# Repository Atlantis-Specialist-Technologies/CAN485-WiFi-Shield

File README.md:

SparkFun AST-CAN485 WiFi Shield
========================================

[*SparkFun AST-CAN485 WiFi Shield (14597)*](https://www.sparkfun.com/products/14597)

The [AST-CAN485 Dev Board](https://www.sparkfun.com/products/14483) brings CAN (Control Area Network) and RS485 to a small, Pro Mini form factor with the ability to interface to 24V input and outputs. When looking to save space, losing the communication cable is one of the best options as well. The SparkFun AST-CAN485 WiFi Shield does just that. With Screw terminal connectors for RS-485 and a U.FL connector, this board supplies solid solutions for working wirelessly in automation, an environment famous for being noisy and unforgiving to electronics. 

The board uses Espressif's ESP8266, a widely used chip in IoT, for wireless communication. The AST-CAN485 WiFi Shield possesses a PCB trace antenna as well as an on-board U.FL connector which allows for external WiFi antennas in situations where more signal strength or distance is needed. An FTDI header is provided as well for working with the ESP8266.

Repository Contents
-------------------

* **/Documentation** - Data sheets, additional product information
* **/Examples/BasicSerial** - Enclosure files 
* **/Hardware** - Eagle design files (.brd, .sch)

Documentation
--------------
* **[Hookup Guide](https://learn.sparkfun.com/tutorials/ast-can485-wifi-shield-hookup-guide)** - Basic hookup guide for the SparkFun AST-CAN485 WiFi Shield.
* **[SparkFun Fritzing repo](https://github.com/sparkfun/Fritzing_Parts)** - Fritzing diagrams for SparkFun products.

License Information
-------------------

This product is _**open source**_! 

Please review the LICENSE.md file for license information. 

If you have any questions or concerns on licensing, please contact techsupport@sparkfun.com.

Distributed as-is; no warranty is given.

- Your friends at SparkFun, in collaboration with Atlantis Specialist Technologies

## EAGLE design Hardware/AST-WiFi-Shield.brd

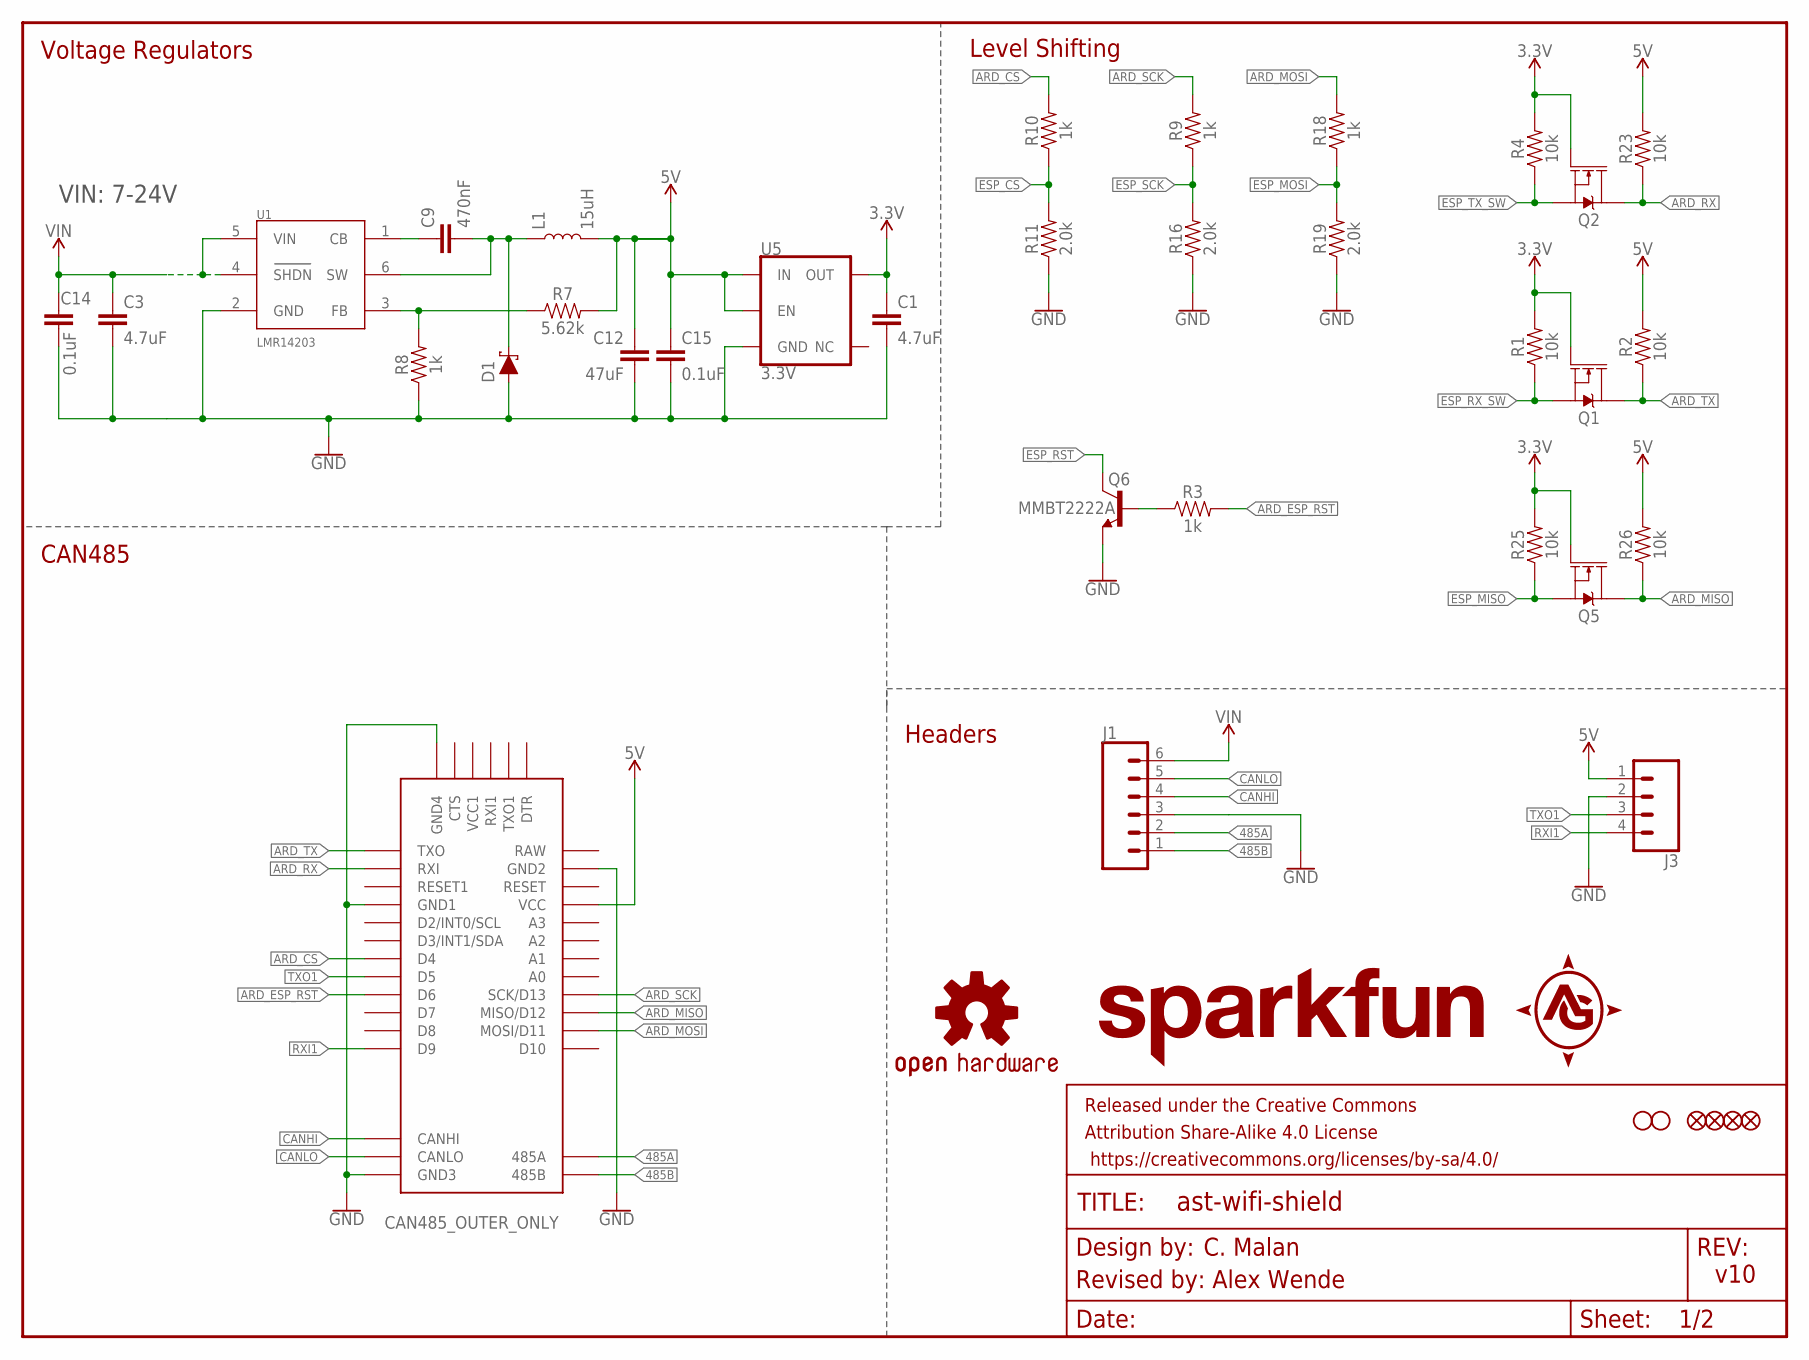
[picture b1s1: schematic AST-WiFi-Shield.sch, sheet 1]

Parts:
C1, C3: 4.7uF; 0603
C9: 470nF; 0603
C12: 47uF; 0805
C14, C15: 0.1uF; 0603
D1: DIODE-SCHOTTKY-MSS1P6-M3/89A; DIODE-MICRO-SMP
FD1, FD2, FD3, FD4: FIDUCIALUFIDUCIAL; FIDUCIAL-MICRO
FRAME2: FRAME-LETTER; CREATIVE_COMMONS
H1, H2: STAND-OFF
J1: CONN_063.5MM-6; SCREWTERMINAL-3.5MM-6
J3: CONN_04LOCK; 1X04_LOCK
L1: 15uH; INDUCTOR_LQH32
LOGO1: OSHW-LOGOS; OSHW-LOGO-S
LOGO2: SFE_LOGO_NAME.2_INCH; SFE_LOGO_NAME_.2
Q1, Q2, Q5: 220mA/50V/3.5Ω; SOT23-3
Q6: MMBT2222A; SOT23-3@1
R1, R2, R4, R23, R25, R26: 10k; 0603
R3, R8, R9, R10, R18: 1k; 0603
R7: 5.62k; 0603
R11, R16, R19: 2.0k; 0603
U1: LMR14203; SOT23-6
U5: 3.3V; SOT23-5
U$2: CAN485_OUTER_ONLY

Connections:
3.3V: C1.1, Q1.1 (G), Q2.1 (G), Q5.1 (G), R1.2, R4.2, R25.2, U5.5 (OUT); also elsewhere on the board
5V: C12.1, C15.1, J3.1, L1.P$2 (2), R2.2, R7.2, R23.2, R26.2, U5.1 (IN), U5.3 (EN), U$2.VCC
485A: J1.2, U$2.485A
485B: J1.1, U$2.485B
ARD_CS: R10.2, U$2.4 (D4)
ARD_ESP_RST: R3.2, U$2.6 (D6)
ARD_MISO: Q5.3 (D), R26.1, U$2.12 (MISO/D12)
ARD_MOSI: R18.2, U$2.11 (MOSI/D11)
ARD_RX: Q2.3 (D), R23.1, U$2.RXI
ARD_SCK: R9.2, U$2.13 (SCK/D13)
ARD_TX: Q1.3 (D), R2.1, U$2.TXO
CANHI: J1.4, U$2.CANHI
CANLO: J1.5, U$2.CANLO
ESP_CS: R10.1, R11.2; also elsewhere on the board
ESP_MISO: Q5.2 (S), R25.1; also elsewhere on the board
ESP_MOSI: R18.1, R19.2; also elsewhere on the board
ESP_RST: Q6.3 (C); also elsewhere on the board
ESP_RX_SW: Q1.2 (S), R1.1; also elsewhere on the board
ESP_SCK: R9.1, R16.2; also elsewhere on the board
ESP_TX_SW: Q2.2 (S), R4.1; also elsewhere on the board
GND: C1.2, C3.2, C12.2, C14.2, C15.2, D1.A, J1.3, J3.2, Q6.2 (E), R8.1, R11.1, R16.1, R19.1, U1.2 (GND), U5.2 (GND), U$2.GND1, U$2.GND2, U$2.GND3, U$2.GND4; also elsewhere on the board
unnamed: C9.1, U1.1 (CB)
unnamed: R7.1, R8.2, U1.3 (FB)
unnamed: Q6.1 (B), R3.1
RXI1: J3.4, U$2.9 (D9)
TXO1: J3.3, U$2.5 (D5)
VIN: C3.1, C14.1, J1.6, U1.4 (SHDN), U1.5 (VIN)
VSW: C9.2, D1.C, L1.P$1 (1), U1.6 (SW)

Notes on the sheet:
Headers
Voltage Regulators
Level Shifting
C. Malan
Revised by: Alex Wende
CAN485
v10
VIN: 7-24V

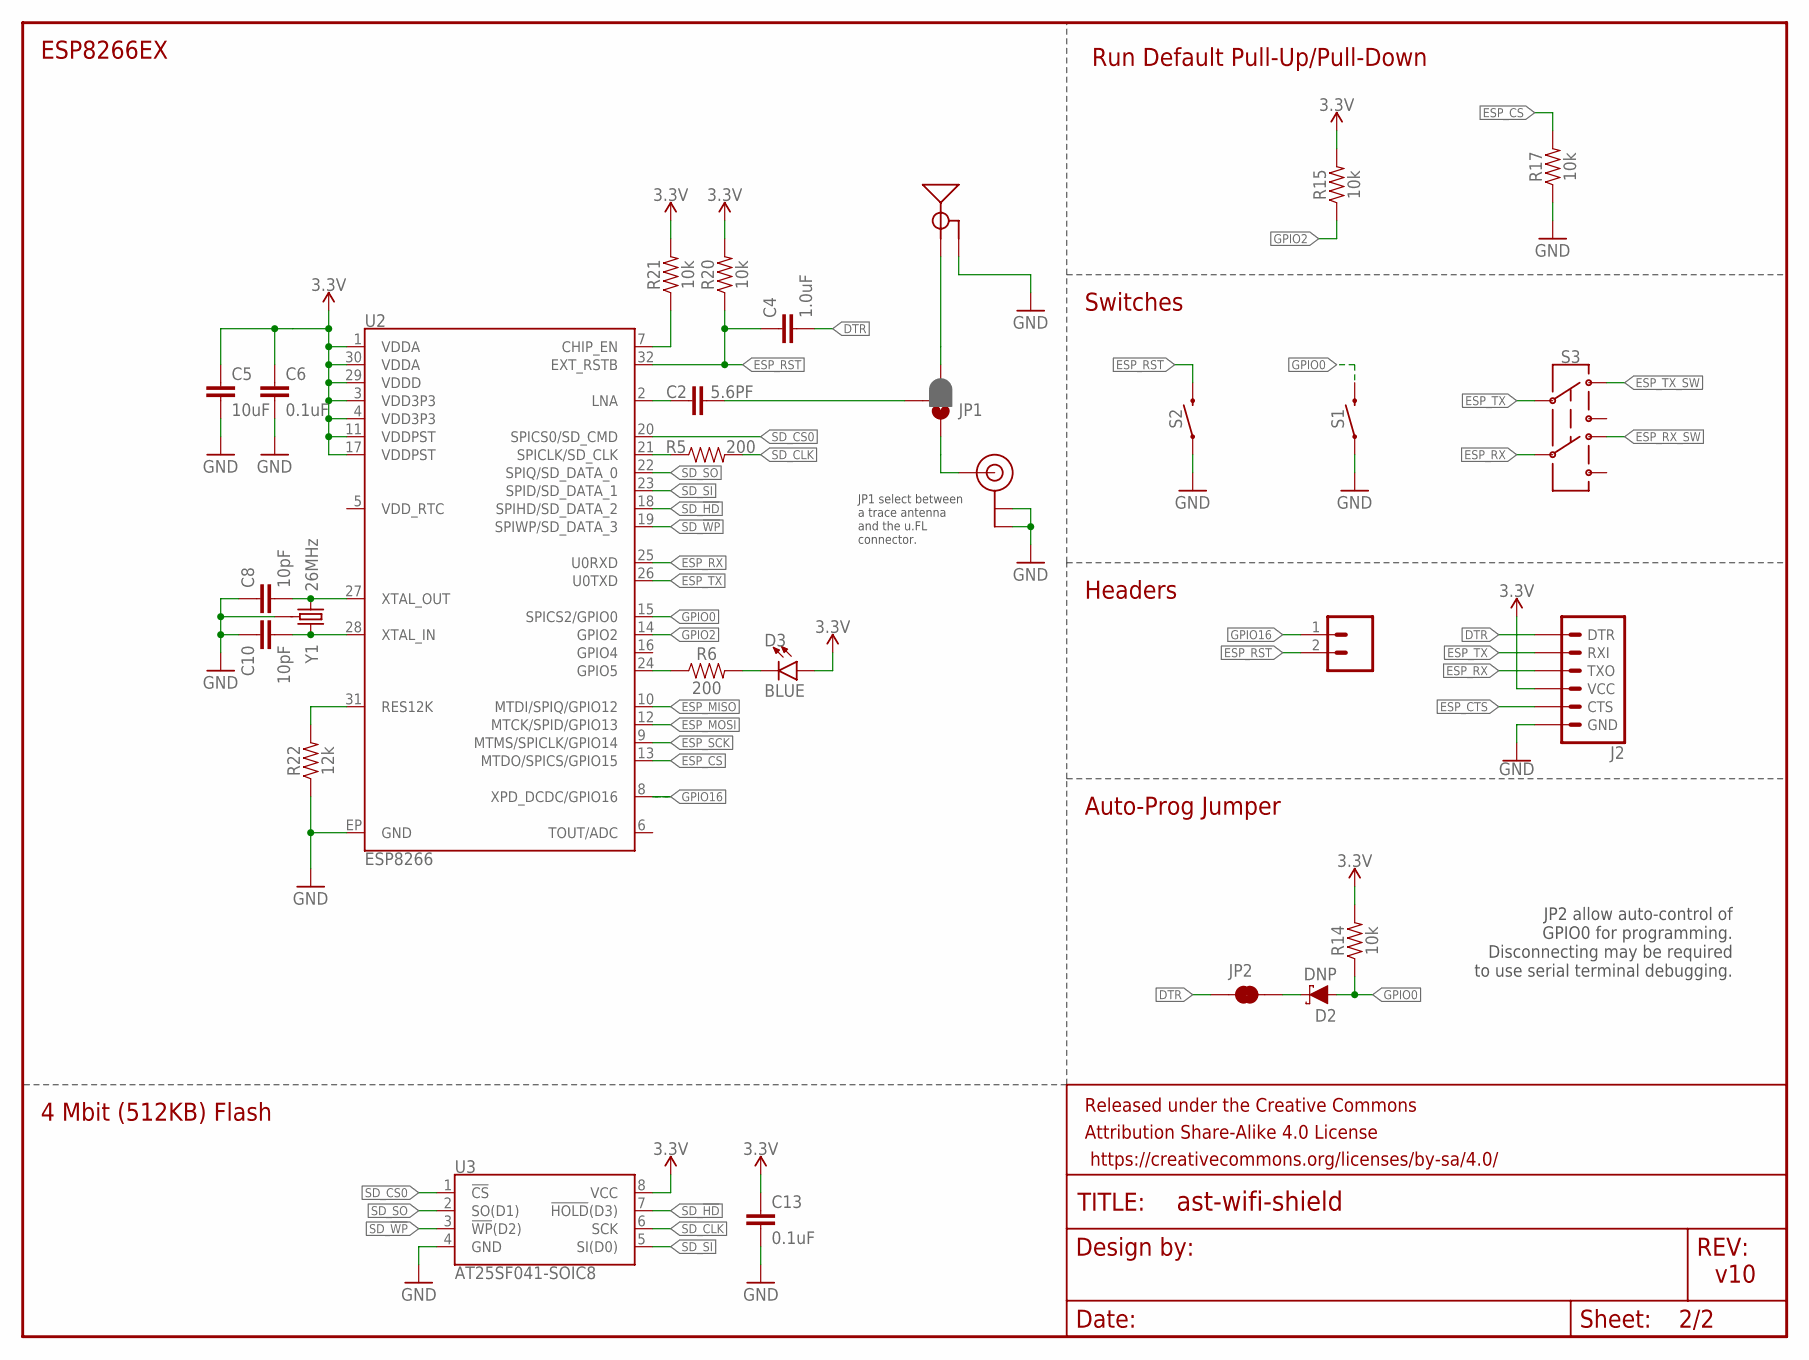
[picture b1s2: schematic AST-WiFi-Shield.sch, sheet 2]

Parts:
C2: 5.6PF; 0603
C4: 1.0uF; 0603
C5: 10uF; 0603
C6, C13: 0.1uF; 0603
C8, C10: 10pF; 0603
D2: DNP; SOD-323
D3: BLUE; LED-0603
E1: ANTENNATRACE; TRACE_ANTENNA_2.4GHZ_25.7MM
E2: U.FL
FRAME3: FRAME-LETTERNO_PACKAGE; DUMMY
J2: 6_PIN_SERIAL_TARGETLOCK; 1X06_LOCK
JP1: JUMPER-SMT_3_1-NC_PASTE_NO-SILK; SMT-JUMPER_3_1-NC_PASTE_NO-SILK
JP2: JUMPER-SMT_2_NC_TRACE_NO-SILK; SMT-JUMPER_2_NC_TRACE_NO-SILK
R5, R6: 200; 0603
R14, R15, R17, R20, R21: 10k; 0603
R22: 12k; 0603
S1, S2: MOMENTARY-SWITCH-SPST-SMD-4.6X2.8MM; TACTILE_SWITCH_SMD_4.6X2.8MM
S3: SWITCH-DPDT-SMD-JS202011JCQN; SWITCH_DPDT_SMD_JS202011JCQN
SJ2: SLEEP-PTH; 1X02_NO_SILK
U2: ESP8266; QFN32
U3: AT25SF041-SOIC8; SO08
Y1: 26MHz; CRYSTAL-SMD-3.2X2.5

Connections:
3.3V: C5.1, C6.1, C13.1, D3.A, J2.4 (VCC), R14.2, R15.2, R20.2, R21.2, U2.1 (VDDA), U2.3 (VDD3P3), U2.4 (VDD3P3), U2.11 (VDDPST), U2.17 (VDDPST), U2.29 (VDDD), U2.30 (VDDA), U3.8 (VCC); also elsewhere on the board
ANT: E2.FEED (SIGNAL), JP1.1
CHIP_EN: R21.1, U2.7 (CHIP_EN)
DTR: C4.2, J2.1 (DTR), JP2.1
ESP_CS: R17.2, U2.13 (MTDO/SPICS/GPIO15); also elsewhere on the board
ESP_CTS: J2.5 (CTS)
ESP_MISO: U2.10 (MTDI/SPIQ/GPIO12); also elsewhere on the board
ESP_MOSI: U2.12 (MTCK/SPID/GPIO13); also elsewhere on the board
ESP_RST: C4.1, R20.1, S2.3 (2), S2.4 (2), SJ2.2, U2.32 (EXT_RSTB); also elsewhere on the board
ESP_RX: J2.3 (TXO), S3.5, U2.25 (U0RXD)
ESP_RX_SW: S3.6 (4); also elsewhere on the board
ESP_SCK: U2.9 (MTMS/SPICLK/GPIO14); also elsewhere on the board
ESP_TX: J2.2 (RXI), S3.2, U2.26 (U0TXD)
ESP_TX_SW: S3.1; also elsewhere on the board
GND: C5.2, C6.2, C8.1, C10.1, C13.2, E1.GND, E1.GND2 (GND), E2.1 (GND), E2.2 (GND), J2.6 (GND), R17.1, R22.1, S1.1, S1.2 (1), S2.1, S2.2 (1), U2.EP (GND), U3.4 (GND), Y1.2 (GND), Y1.4 (GND); also elsewhere on the board
GPIO0: D2.A, R14.1, S1.3 (2), S1.4 (2), U2.15 (SPICS2/GPIO0)
GPIO2: R15.1, U2.14 (GPIO2)
GPIO5: R6.1, U2.24 (GPIO5)
GPIO16: SJ2.1, U2.8 (XPD_DCDC/GPIO16)
unnamed: D2.C, JP2.2
unnamed: R22.2, U2.31 (RES12K)
unnamed: C10.2, U2.28 (XTAL_IN), Y1.3 (2)
unnamed: C8.2, U2.27 (XTAL_OUT), Y1.1
unnamed: C2.1, U2.2 (LNA)
unnamed: C2.2, JP1.2
unnamed: D3.C, R6.2
SD_!HD!: U2.18 (SPIHD/SD_DATA_2), U3.7 (!HOLD!(D3))
SD_!WP!: U2.19 (SPIWP/SD_DATA_3), U3.3 (!WP!(D2))
SD_CLK: R5.2, U3.6 (SCK)
SD_CLK0: R5.1, U2.21 (SPICLK/SD_CLK)
SD_CS0: U2.20 (SPICS0/SD_CMD), U3.1 (!CS!)
SD_SI: U2.23 (SPID/SD_DATA_1), U3.5 (SI(D0))
SD_SO: U2.22 (SPIQ/SD_DATA_0), U3.2 (SO(D1))
TRACE_ANT: E1.ANT (SIGNAL), JP1.3

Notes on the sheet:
JP1 select between a trace antenna and the u.FL connector.
ESP8266EX
Auto-Prog Jumper
Run Default Pull-Up/Pull-Down
4 Mbit (512KB) Flash
Headers
Switches
v10
JP2 allow auto-control of GPIO0 for programming. Disconnecting may be required to use serial terminal debugging.

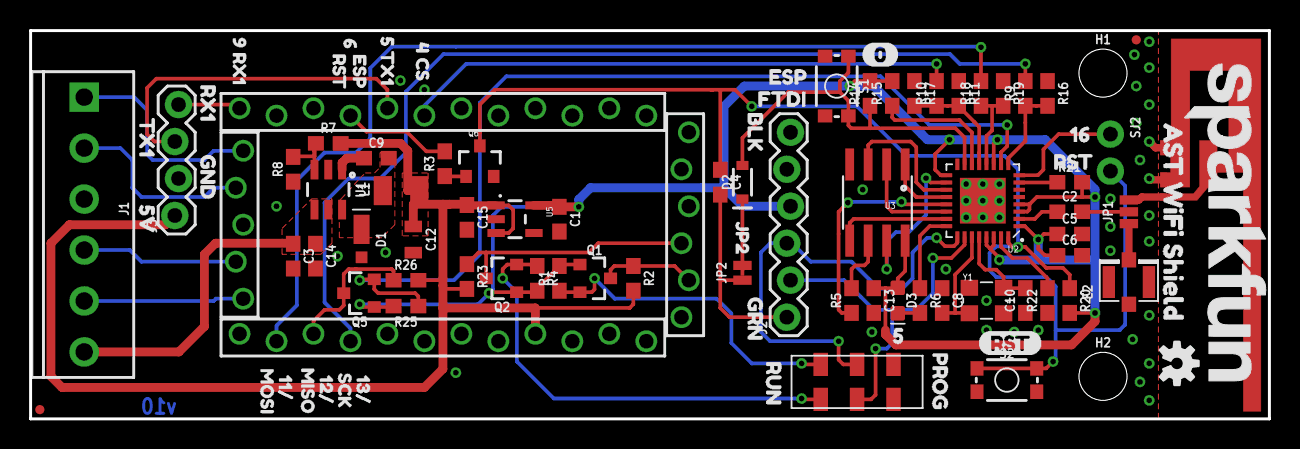
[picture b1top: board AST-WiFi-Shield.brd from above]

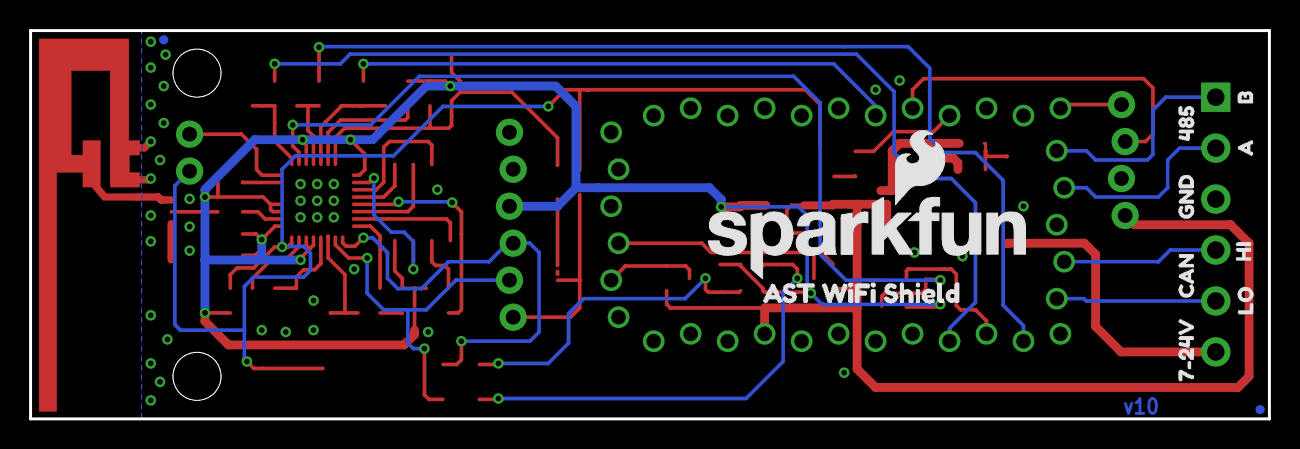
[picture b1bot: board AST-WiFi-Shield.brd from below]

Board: 2 copper layers, 85.1 x 26.7 mm, 110 parts (12 on the bottom side), 52 nets.

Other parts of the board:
U$1: _9_RX12
U$3: 5_TX11
U$4: 612
U$5: _ESP4
U$6: _RST5
U$7: 7#24V0
U$8: GRN2
U$9: BLK3
U$10: _MOSI7
U$11: 12#1
U$12: 13#2
U$13: RX14
U$14: TX15
U$15: GND6
U$16: 5V7
U$17: 00
U$18: RST1
U$19: MISO8
U$20: SCK11
U$21: GND10
U$22: CAN11
U$23: HI26
U$24: LO27
U$25: 48518
U$27: JP23
U$28: 11#0
U$29: A33
U$30: B34
U$32, U$35: AST_WIFI_SHIELD0
U$33: SFE_LOGO_NAME_FLAME_.2
U$36: FTDI7
U$37: 168
U$38: ESP22
U$39: RST23
U$40: 52
U$41: RUN1
U$42: PROG0
U$43: 4_CS0

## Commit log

2019-02-14 Readme
2019-02-14 Documentation and Readme
    Update readme with placeholder links
2019-02-14 License information
2019-02-15 Update README.md
    Updating ReadMe with SparkFun formatted links and Text
2019-02-15 Update README.md
    Fixing Copy Paste error. :D
2019-02-15 Create License.md
    Adding standard SparkFun license file

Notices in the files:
parts and their libraries:
SparkFun-Capacitors: Licensing: Creative Commons ShareAlike 4.0 International - https://creativecommons.org/licenses/by-sa/4.0
SparkFun-Aesthetics: Released under the Creative Commons Attribution Share-Alike 4.0 License
SparkFun-Aesthetics: https://creativecommons.org/licenses/by-sa/4.0
